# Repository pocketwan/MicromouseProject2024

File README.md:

A micromouse is an electro-mechanical robot that is designed to find the shortest path in a maze without hitting the walls of the maze. The micromouse consists of a power subsystem which enables the micromouse to move forwards or backwards in the maze and to turn left or right. It also consists of a sensing subsystem which enables the micromouse to detect the walls of the maze in order to avoid hitting them. The scope of this project is to design and manufacture the power and the sensing subsystems of the micromouse that will assist the micromouse in navigating through the maze. This project forms part of a larger project which entails designing an algorithm that will enable a micromouse to determine the shortest path in a maze with dead ends and multiple paths to the finishing point.

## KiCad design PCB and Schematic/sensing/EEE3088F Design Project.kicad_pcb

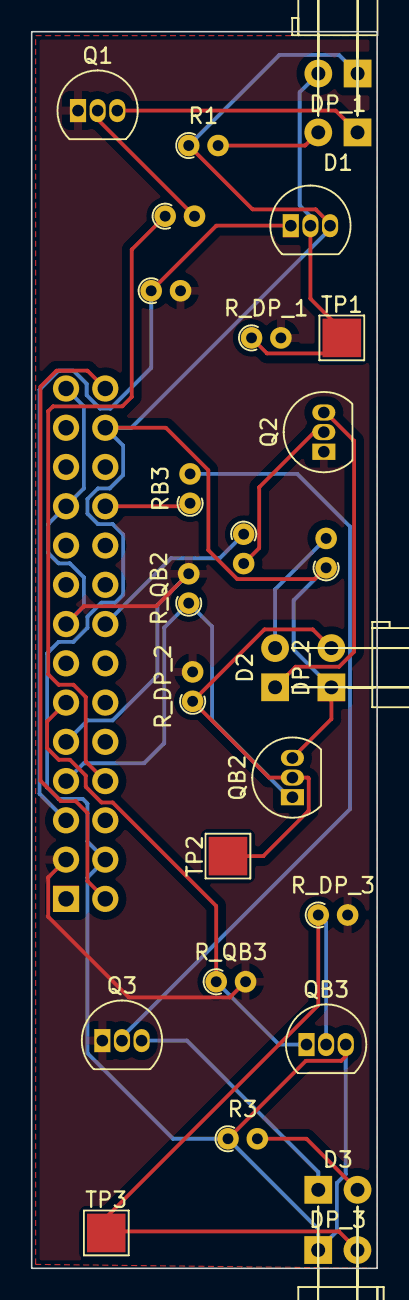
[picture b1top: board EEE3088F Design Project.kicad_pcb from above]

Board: 2 copper layers, 22.4 x 80.0 mm, 28 parts (1 on the bottom side), 21 nets.

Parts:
D1, D2, D3: IR LED; LED_D5.0mm_Horizontal_O6.35mm_Z9.0mm
DP_1, DP_2, DP_3: Photodiode; LED_D5.0mm_Horizontal_O6.35mm_Z3.0mm
J1: Conn_02x14_Odd_Even; PinHeader_2x14_P2.54mm_Vertical
Q1, Q2, Q3: 2N3904; TO-92_Inline
QB1, QB2, QB3: 2N3904; TO-92_Inline
R1, R2, R3: 47; R_Axial_DIN0204_L3.6mm_D1.6mm_P1.90mm_Vertical
RB1, RB2, RB3: 5.1k; R_Axial_DIN0204_L3.6mm_D1.6mm_P1.90mm_Vertical
R_DP_1, R_DP_2, R_DP_3: 1M; R_Axial_DIN0204_L3.6mm_D1.6mm_P1.90mm_Vertical
R_QB1, R_QB2, R_QB3: 10k; R_Axial_DIN0204_L3.6mm_D1.6mm_P1.90mm_Vertical
TP1: Test1; TestPoint_Pad_2.5x2.5mm
TP2: Test2; TestPoint_Pad_2.5x2.5mm
TP3: Test3; TestPoint_Pad_2.5x2.5mm

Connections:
+3V3: J1.2, J1.28
/BATT: DP_1.1 (K), DP_2.1 (K), DP_3.1 (K), J1.4, J1.26, QB1.3 (C), QB2.3 (C), QB3.3 (C), R1.1, R2.1, R3.1
/PA3: J1.5, QB1.1 (E), R_QB1.1
/PA4: J1.7, QB2.1 (E), R_QB2.1
/PA5: J1.11, QB3.1 (E), R_QB3.1
/PE8: J1.22, RB3.1
/PE11: J1.16, RB2.1
/PE15: J1.8, RB1.1
/VO1: DP_1.2 (A), QB1.2 (B), R_DP_1.1, TP1.1
/VO2: DP_2.2 (A), QB2.2 (B), R_DP_2.1, TP2.1
/VO3: DP_3.2 (A), QB3.2 (B), R_DP_3.1, TP3.1
GND: J1.3, J1.9, J1.15, J1.21, J1.27, Q1.1 (E), Q2.1 (E), Q3.1 (E), R_DP_1.2, R_DP_2.2, R_DP_3.2, R_QB1.2, R_QB2.2, R_QB3.2
unnamed: D1.1 (K), Q1.3 (C)
unnamed: D1.2 (A), R1.2
unnamed: D2.1 (K), Q2.3 (C)
unnamed: D2.2 (A), R2.2
unnamed: D3.1 (K), Q3.3 (C)
unnamed: D3.2 (A), R3.2
unnamed: Q1.2 (B), RB1.2
unnamed: Q2.2 (B), RB2.2
unnamed: Q3.2 (B), RB3.2

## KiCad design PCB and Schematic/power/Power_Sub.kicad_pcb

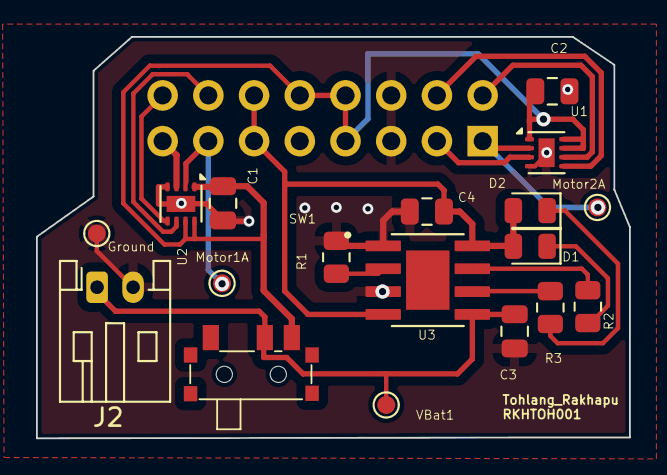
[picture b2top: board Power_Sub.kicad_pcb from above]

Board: 2 copper layers, 32.9 x 22.3 mm, 19 parts (1 on the bottom side), 17 nets.

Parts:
C1, C2: 0.1uF; C_0805_2012Metric
C3, C4: 10uF; C_0805_2012Metric
D1: GREEN_LED; LED_0805_2012Metric
D2: RED_LED; LED_0805_2012Metric
Ground: TestPoint; TestPoint_Pad_D1.0mm
J1: Conn_02x08_Odd_Even; PinHeader_2x08_P2.54mm_Vertical
J2: Conn_01x02_Pin; JST_PH_S2B-PH-K_1x02_P2.00mm_Horizontal
Motor1A, Motor2A: TestPoint; TestPoint_Pad_D1.0mm
R1: 3k3; R_0805_2012Metric
R2, R3: 1k; R_0805_2012Metric
SW1: SW_DPDT_x2; mySwitch
U1, U2: DRV8837C; WSON-8-1EP_2x2mm_P0.5mm_EP0.9x1.6mm
U3: TP4056; SOP127P600X175-9N
VBat1: TestPoint; TestPoint_Pad_D1.0mm

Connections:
+5V: C4.1, D1.2 (A), D2.2 (A), J1.11, J1.12, U3.4 (VCC), U3.8 (CE)
/BATT: C3.1, J2.1, SW1.2 (B), U3.5 (BAT), VBat1.1
/Motor1_A: J1.13, Motor1A.1, U2.2 (OUT1)
/Motor1_B: J1.15, U2.3 (OUT2)
/Motor2_A: J1.1, Motor2A.1, U1.2 (OUT1)
/Motor2_B: J1.3, U1.3 (OUT2)
/PWM1: J1.2, U1.6 (IN1)
/PWM2: J1.4, U1.5 (IN2)
/PWM3: J1.14, U2.6 (IN1)
/PWM4: J1.16, U2.5 (IN2)
GND: C1.2, C2.2, C3.2, C4.2, Ground.1, J1.5, J1.6, J2.2, R1.2, U1.4 (GND), U1.9 (GND), U2.4 (GND), U2.9 (GND), U3.1 (TEMP), U3.3 (GND)
unnamed: D1.1 (K), R2.1
unnamed: D2.1 (K), R3.1
unnamed: R1.1, U3.2 (PROG)
unnamed: R2.2, U3.7 (~CHRG)
unnamed: R3.2, U3.6 (~STDBY)
VDC: C1.1, C2.1, J1.7, J1.8, J1.10, SW1.3 (C), U1.1 (VM), U1.7 (~SLEEP), U1.8 (VCC), U2.1 (VM), U2.7 (~SLEEP), U2.8 (VCC)

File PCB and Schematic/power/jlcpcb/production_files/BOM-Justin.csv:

Comment,Designator,Footprint,LCSC
10uF,"C3,C4",C_0805_2012Metric,C15850
TP4056,U3,SOP127P600X175-9N,C16581
100R,"R2,R3",R_0805_2012Metric,C17408
DRV8837C,"U1,U2",WSON-8-1EP_2x2mm_P0.5mm_EP0.9x1.6mm,C191000
RED_LED,D2,LED_0805_2012Metric,C2296
GREEN_LED,D1,LED_0805_2012Metric,C2297
3k3,R1,R_0805_2012Metric,C26010
0.1uF,"C1,C2",C_0805_2012Metric,C28233
SW_DPDT_x2,SW1,mySwitch,C2890358

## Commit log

2024-03-21 Add files via upload
    Adding schematic and PCB files for the sensing module of the Micromouse project.
2024-03-21 Rename EEE3088F Design Project.kicad_pcb to empty.txt
2024-03-21 Rename EEE3088F Design Project.kicad_prl to PCB and Schematic/EEE3088F Design Project.kicad_prl
2024-03-21 Rename EEE3088F Design Project.kicad_pro to PCB and Schematic/EEE3088F Design Project.kicad_pro
2024-03-21 Update and rename fp-info-cache to PCB and Schematic/fp-info-cache
2024-03-21 Rename PCB and Schematic/EEE3088F Design Project.kicad_prl to PCB and Schematic/sensing/EEE3088F Design Project.kicad_prl
2024-03-21 Rename PCB and Schematic/EEE3088F Design Project.kicad_pro to PCB and Schematic/sensing/EEE3088F Design Project.kicad_pro
2024-03-21 Update and rename PCB and Schematic/fp-info-cache to PCB and Schematic/sensing/fp-info-cache
2024-03-24 Delete PCB and Schematic/sensing/EEE3088F Design Project2.kicad_sch
    Deleted file
2024-04-05 Create power.txt
    Testing
2024-04-05 Uploading the power subsystem files.
2024-04-06 changed the file structure of the repository
